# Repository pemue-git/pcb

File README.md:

Dieses Werk ist lizenziert unter einer [Creative Commons Namensnennung - Nicht-kommerziell - Weitergabe unter gleichen Bedingungen 4.0 International Lizenz](http://creativecommons.org/licenses/by-nc-sa/4.0/).

# PCB
This repository contains several PCBs for home automation, discussions see FHEM forum: [forum.fhem.de](https://forum.fhem.de)

## Communication PCB for a Panasonic heat pump
Communication PCB for a Panasonic WH-MDC05f3e5 heat pump also called "Geisha": [WH-MDC05F3E5_comm](WH-MDC05F3E5_comm)

## **L**aCrosse **G**ate**W**ay
ESP8266 based gateway for LaCrosse sensors inlcuding extension PCB.

## nanoCUL
Several versions for a CC1101 USB Light

## Optolink
Interface for Viessmann heating and solar controls (USB, RaspberryPi and WLAN)

Firmware for Optolink interface can be found in [vitotronic-interface](https://github.com/pemue-git/vitotronic_interface).

## Homematic sensors
Several versions of Homematic sensors for usage inside and outside:

Based on [Dirk's version](https://wiki.fhem.de/wiki/Universalsensor) of the sensor, several modifications of the [outside sensor](homematic/aussensensor) have been made.

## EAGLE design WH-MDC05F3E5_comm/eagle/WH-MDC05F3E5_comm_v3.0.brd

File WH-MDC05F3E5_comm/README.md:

# Communication PCB for a Panasonic heat pump
Communication PCB for a Panasonic [WH-MDC05f3e5](http://aquarea.smallsolutions.de/index.php?title=WH-MDC05f3e5) heat pump also called "Geisha". This PCB is based on a schematic posted [here](https://forum.fhem.de/index.php/topic,80916.msg879068.html#msg879068).

# Changelog

* v2.0 (throughole version)
  * based on this [schematic](https://forum.fhem.de/index.php/topic,80916.msg879068.html#msg879068)
  * added static signal on unused gates
  * schematic

* v3.0 (SMD version)
  * all parts changed to SMD
  * layout top

  * layout bottom

  * assembled PCB and USB2serial converter

  * assembled PCB and USB2serial converter (Waveshare)

  * assembled PCB and USB2serial converter (bottom view)

  * [schematic](WH-MDC05F3E5_comm_v3.0_sch.pdf)
  * [gerber files](gerber/WH-MDC05F3E5_comm_v3.0_gerber.zip)
  * [bill of material](WH-MDC05F3E5_comm_v3.0_bom.xls)

# Assembly
__CAUTION__: Pin 1 marking of 4011B is a chamfer at the IC package, indicating the position of pin 1 (chamfer at the left).  
Necessary for the communication is an USB2serial converter (needed signals: 3.3 V, GND, RxD, TxD and __RTS__). The controller chip needs to be a [CP2102](https://www.silabs.com/documents/public/data-sheets/CP2102-9.pdf) and __RTS__ pin needs to be available. The baud rate needs to be set to [960 baud](https://forum.fhem.de/index.php/topic,80916.msg729625.html#msg729625).
An example for a suitable USB2serial converter is [here](https://www.reichelt.de/entwicklerboards-microusb-buchse-auf-uart-cp2102-debo-musb2uart-2-p266052.html?CCOUNTRY=445&LANGUAGE=de&trstct=pos_0&nbc=1&&r=1).

# Modification
The schematic and board files are compatible with EAGLE v6.x.

# Resources
* [WH-MDC05f3e5 documents](http://aquarea.smallsolutions.de/index.php?title=WH-MDC05f3e5#Links_zu_Original_Dokumenten)
* [WiFi module for WH-MDC05f3e5](https://www.haustechnikdialog.de/Forum/t/181931/Intensishome-Wifi-Modul-in-Kombination-mit-der-Panasonic-WH-MDC05F3E5-Geisha) and discussion in Haustechnik Forum
* [PCB hardware discussion](https://forum.fhem.de/index.php/topic,104628.msg985249.html#msg985249) in FHEM forum
* [setup of communcation PCB](https://forum.fhem.de/index.php/topic,80916.msg729625.html#msg729625) in FHEM forum
* [FHEM control](http://aquarea.smallsolutions.de/index.php?title=Steuerung_via_FHEM) in aquarea forum
* [FHEM module](https://github.com/der-lolo/aquarea)
* [Tweakers forum](https://gathering.tweakers.net/forum/list_message/64194378#64194378) (NL)
* for documentation purposes: [online check of MD files](https://dillinger.io/)

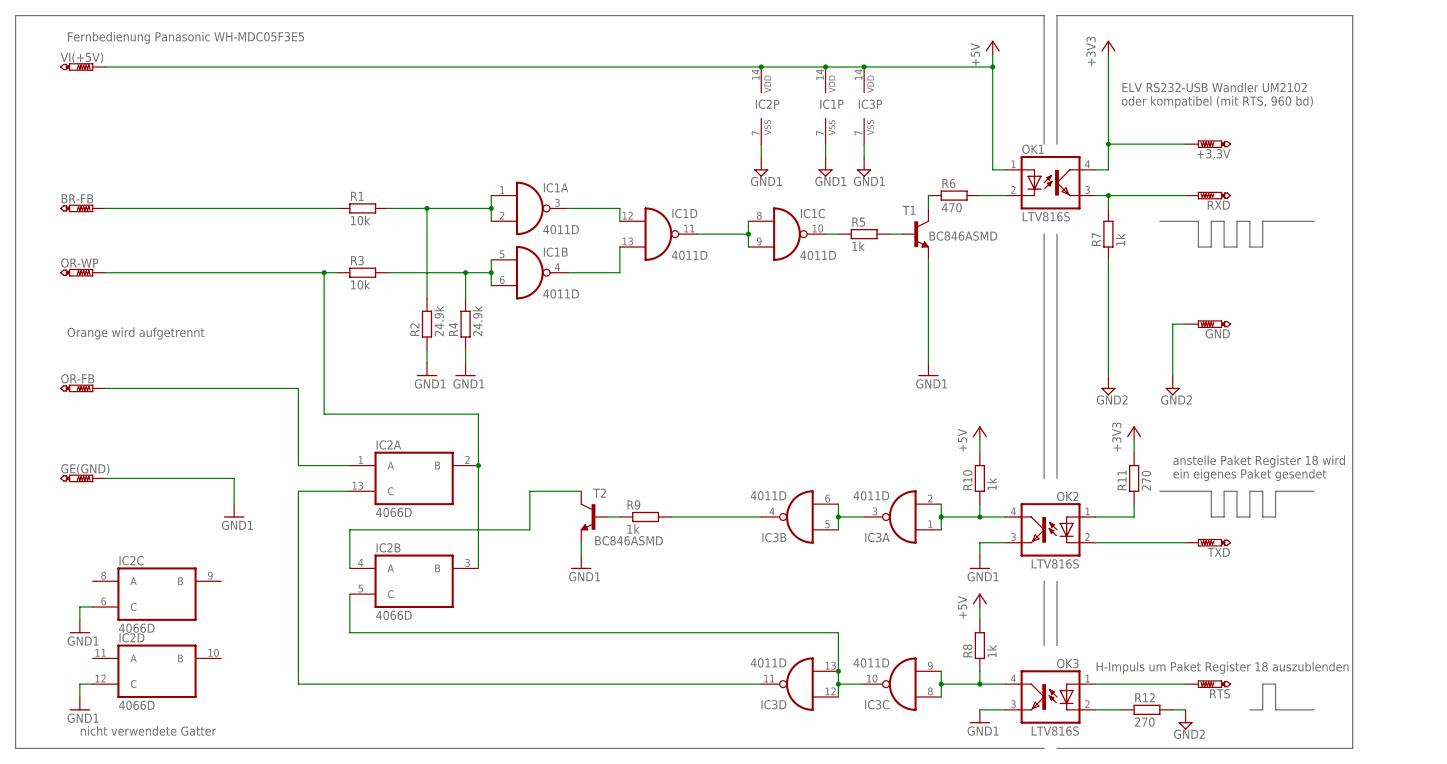
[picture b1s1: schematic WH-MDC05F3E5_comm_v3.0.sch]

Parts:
+3,3V: PTR1PAD1-17; P1-17
BR-FB: PTR1PAD1-17; P1-17
GE(GND): PTR1PAD1-17; P1-17
GND: PTR1PAD1-17; P1-17
IC1, IC3: 4011D; SO14
IC2: 4066D; SO14
OK1, OK2, OK3: LTV816S; SMD4
OR-FB: PTR1PAD1-17; P1-17
OR-WP: PTR1PAD1-17; P1-17
R1, R3: 10k; R0805
R2, R4: 24.9k; R0805
R5, R7, R8, R9, R10: 1k; R0805
R6: 470; R0805
R11, R12: 270; R0805
RTS: PTR1PAD1-17; P1-17
RXD: PTR1PAD1-17; P1-17
T1, T2: BC846ASMD; SOT23
TXD: PTR1PAD1-17; P1-17
VI(+5V): PTR1PAD1-17; P1-17

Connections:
+3V3: +3,3V.TP, OK1.4 (COL), R11.2
+5V: IC1.14 (VDD), IC2.14 (VDD), IC3.14 (VDD), OK1.1 (A), R8.2, R10.2, VI(+5V).TP
GND1: GE(GND).TP, IC1.7 (VSS), IC2.6 (C), IC2.7 (VSS), IC2.12 (C), IC3.7 (VSS), OK2.3 (EMIT), OK3.3 (EMIT), R2.1, R4.1, T1.2 (E), T2.2 (E)
GND2: GND.TP, R7.1, R12.2
unnamed: IC1.1 (I0), IC1.2 (I1), R1.2, R2.2
unnamed: IC1.5 (I0), IC1.6 (I1), R3.2, R4.2
unnamed: IC1.3 (O), IC1.12 (I0)
unnamed: IC1.4 (O), IC1.13 (I1)
unnamed: IC1.8 (I0), IC1.9 (I1), IC1.11 (O)
unnamed: IC1.10 (O), R5.1
unnamed: R5.2, T1.1 (B)
unnamed: R6.2, T1.3 (C)
unnamed: OK1.2 (C), R6.1
unnamed: OK1.3 (EMIT), R7.2, RXD.TP
unnamed: IC2.4 (A), T2.3 (C)
unnamed: OK2.1 (A), R11.1
unnamed: IC2.1 (A), OR-FB.TP
unnamed: IC2.2 (B), IC2.3 (B), OR-WP.TP, R3.1
unnamed: BR-FB.TP, R1.1
unnamed: OK2.2 (C), TXD.TP
unnamed: IC2.13 (C), IC3.11 (O)
unnamed: IC3.8 (I0), IC3.9 (I1), OK3.4 (COL), R8.1
unnamed: IC2.5 (C), IC3.10 (O), IC3.12 (I0), IC3.13 (I1)
unnamed: OK3.2 (C), R12.1
unnamed: OK3.1 (A), RTS.TP
unnamed: IC3.1 (I0), IC3.2 (I1), OK2.4 (COL), R10.1
unnamed: IC3.3 (O), IC3.5 (I0), IC3.6 (I1)
unnamed: R9.1, T2.1 (B)
unnamed: IC3.4 (O), R9.2

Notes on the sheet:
Fernbedienung Panasonic WH-MDC05F3E5
ELV RS232-USB Wandler UM2102 oder kompatibel (mit RTS, 960 bd)
H-Impuls um Paket Register 18 auszublenden
Orange wird aufgetrennt
anstelle Paket Register 18 wird ein eigenes Paket gesendet
nicht verwendete Gatter

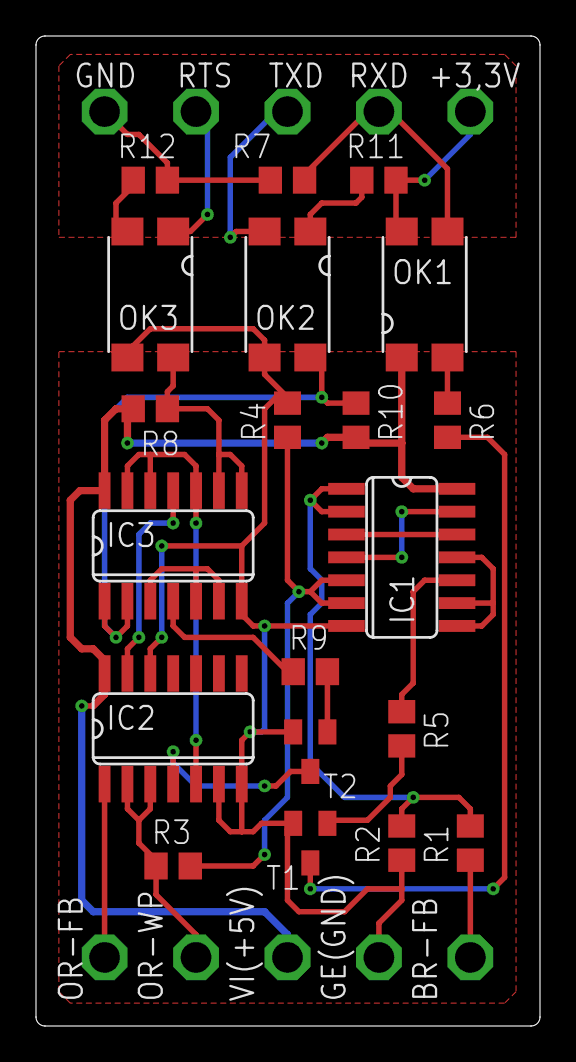
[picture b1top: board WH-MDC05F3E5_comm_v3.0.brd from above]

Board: 2 copper layers, 28.0 x 55.0 mm, 30 parts (0 on the bottom side), 29 nets.

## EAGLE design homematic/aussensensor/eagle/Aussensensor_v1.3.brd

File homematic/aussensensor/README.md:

# Homematic
This repository contains several PCBs for Homematic sensors for usage outside (*Aussensensor*).

## Aussensensor
This layout is based on Dirk's *Universalsensor* described [here](https://wiki.fhem.de/wiki/Universalsensor).

v1.2 schematic of the layout can be found [here](https://github.com/kc-GitHub/Wettersensor/blob/master/Schematic/Universal-Sensor_Atmega328.sch) and board [here](https://github.com/kc-GitHub/Wettersensor/blob/master/Schematic/Universal-Sensor_Atmega328.brd).

v1.2 gerber files can be found [here](Aussensensor_v1.2_gerber).

### Changelog

* v1.3 (06/15/2018, PeMue)
  * GDO2 of CC1101 module connected to D3
  * BME280 added (temperature, pressure, humidity)

* v1.4 (07/09/2018, PeMue)
  * GDO2 removed, added additional capacitor to CC1101 module
  * DS18B20 and pullup to 3.3 V connected to D3, supply voltage is 3.3V
  * added additional tantalum capacitor to MAX1724 output
  * changed pinout of I2C connector to match pinning of MAX44009 light sensor module
  * added SJ2 for battery voltage measurement w/o battery load
  * layout (top)
    
  * layout (bot)

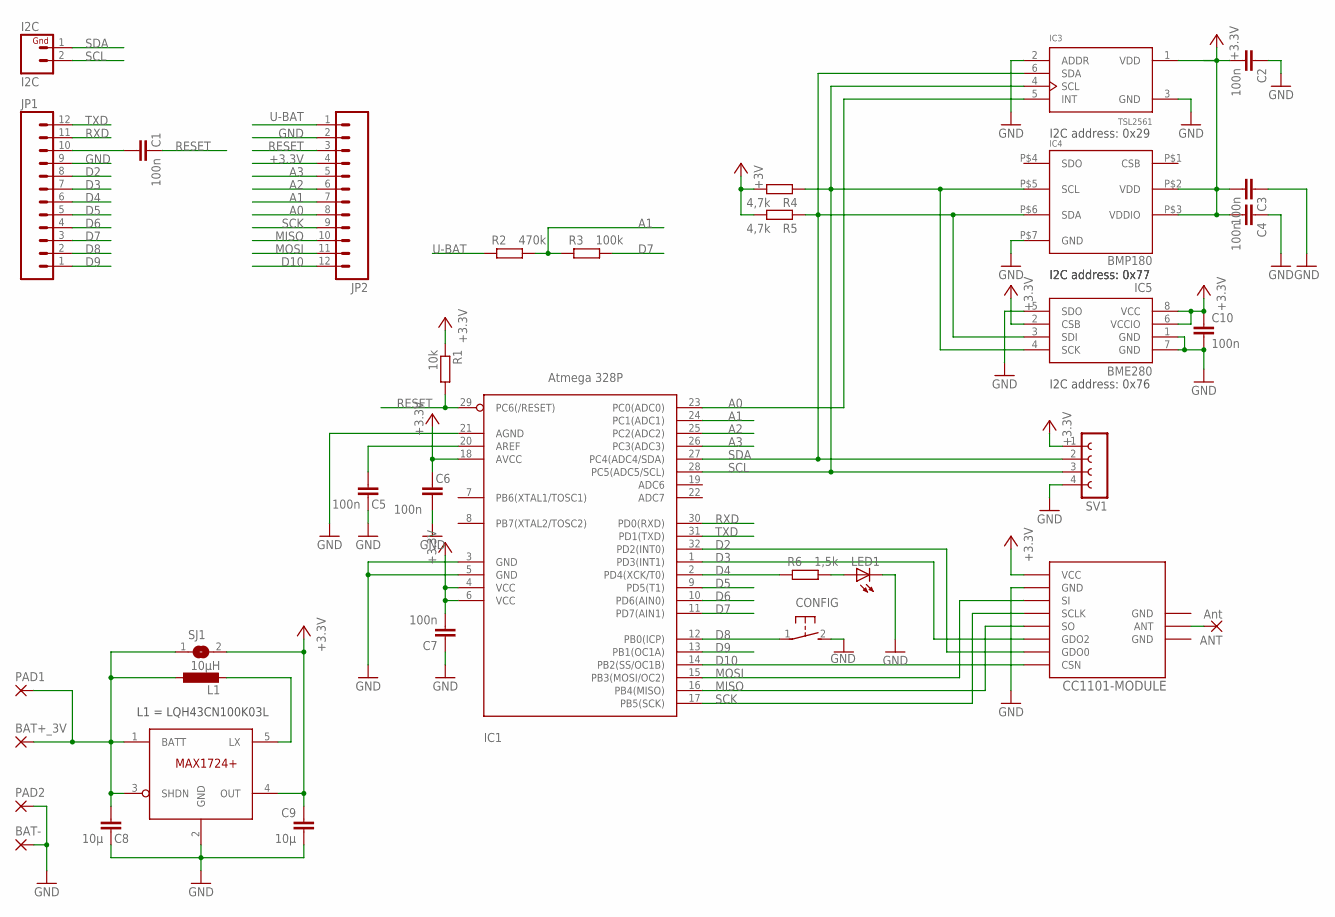
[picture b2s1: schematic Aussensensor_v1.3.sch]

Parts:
ANT: Ant; 1,6/0,8
BAT+_3V: 1,6/0,9
BAT-: 1,6/0,9
C1, C2, C3, C4, C5, C6, C7, C10: 100n; C0805
C8, C9: 10µ; C1206
CC1101-MODULE: CC1101_WIRELES_MODULE
CONFIG: DTSM-3
I2C: I2C; 1X02
IC1: Atmega 328P; TQFP32-08
IC2: MAX1724; SOT23-5L
IC3: TSL2561; TMB-6
IC4: BMP180; LGA-7
IC5: BME280; LGA_8PIN_25X25
JP1, JP2: M12PTH; 1X12
L1: 10µH; L4532P
LED1: LEDCHIP-LED0805; CHIP-LED0805
PAD1, PAD2: SMD2; SMD1,27-2,54
R1: 10k; M0805
R2: 470k; M0805
R3: 100k; M0805
R4, R5: 4,7k; M0805
R6: 1,5k; M0805
SJ1: SJ
SV1: FE04-1

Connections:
+3.3V: C2.2, C3.2, C4.2, C6.2, C7.2, C9.2, C10.1, CC1101-MODULE.VCC, IC1.4 (VCC), IC1.6 (VCC), IC1.18 (AVCC), IC2.4 (OUT), IC3.1 (VDD), IC4.P$2 (VDD), IC4.P$3 (VDDIO), IC5.2 (CSB), IC5.6 (VCCIO), IC5.8 (VCC), JP2.4, R1.1, R4.2, R5.2, SJ1.2, SV1.1
A0: IC1.23 (PC0(ADC0)), IC3.5 (INT), JP2.8
A1: IC1.24 (PC1(ADC1)), JP2.7, R2.2, R3.1
A2: IC1.25 (PC2(ADC2)), JP2.6
A3: IC1.26 (PC3(ADC3)), JP2.5
D2: CC1101-MODULE.GDO0, IC1.32 (PD2(INT0)), JP1.8
D3: CC1101-MODULE.GDO2, IC1.1 (PD3(INT1)), JP1.7
D4: IC1.2 (PD4(XCK/T0)), JP1.6, R6.1
D5: IC1.9 (PD5(T1)), JP1.5
D6: IC1.10 (PD6(AIN0)), JP1.4
D7: IC1.11 (PD7(AIN1)), JP1.3, R3.2
D8: CONFIG.1, IC1.12 (PB0(ICP)), JP1.2
D9: IC1.13 (PB1(OC1A)), JP1.1
D10: CC1101-MODULE.CSN, IC1.14 (PB2(SS/OC1B)), JP2.12
GND: BAT-.1, C2.1, C3.1, C4.1, C5.1, C6.1, C7.1, C8.1, C9.1, C10.2, CC1101-MODULE.GND@1 (GND), CC1101-MODULE.GND@2 (GND), CC1101-MODULE.GND@3 (GND), CONFIG.2, IC1.3 (GND), IC1.5 (GND), IC1.21 (AGND), IC2.2 (GND), IC3.2 (ADDR), IC3.3 (GND), IC4.P$7 (GND), IC5.1 (GND), IC5.5 (SDO), IC5.7 (GND), JP1.9, JP2.2, LED1.C, PAD2.1, SV1.4
MISO: CC1101-MODULE.SO, IC1.16 (PB4(MISO)), JP2.10
MOSI: CC1101-MODULE.SI, IC1.15 (PB3(MOSI/OC2)), JP2.11
unnamed: C1.2, JP1.10
unnamed: IC2.5 (LX), L1.2
unnamed: LED1.A, R6.2
unnamed: ANT.1, CC1101-MODULE.ANT
unnamed: C5.2, IC1.20 (AREF)
RESET: C1.1, IC1.29 (PC6(/RESET)), JP2.3, R1.2
RXD: IC1.30 (PD0(RXD)), JP1.11
SCK: CC1101-MODULE.SCLK, IC1.17 (PB5(SCK)), JP2.9
SCL: I2C.2, IC1.28 (PC5(ADC5/SCL)), IC3.4 (SCL), IC4.P$5 (SCL), IC5.4 (SCK), R4.1, SV1.3
SDA: I2C.1, IC1.27 (PC4(ADC4/SDA)), IC3.6 (SDA), IC4.P$6 (SDA), IC5.3 (SDI), R5.1, SV1.2
TXD: IC1.31 (PD1(TXD)), JP1.12
U-BAT: BAT+_3V.1, C8.2, IC2.1 (BATT), IC2.3 (SHDN), JP2.1, L1.1, PAD1.1, R2.1, SJ1.1

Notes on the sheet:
L1 = LQH43CN100K03L
I2C address: 0x29
I2C address: 0x77
I2C address: 0x76

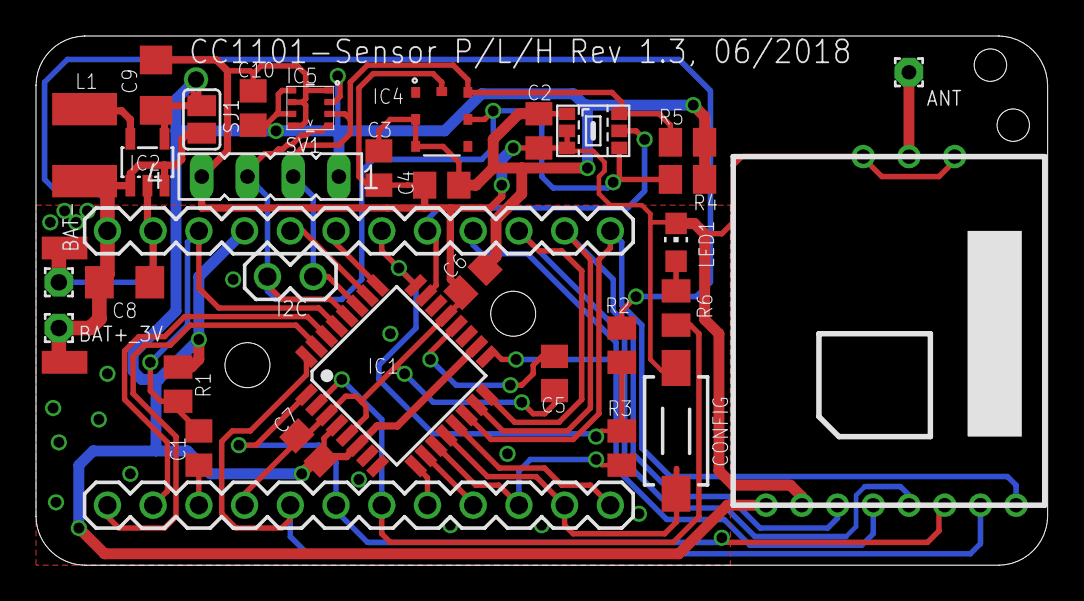
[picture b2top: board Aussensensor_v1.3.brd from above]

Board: 2 copper layers, 56.2 x 29.4 mm, 35 parts (0 on the bottom side), 29 nets.

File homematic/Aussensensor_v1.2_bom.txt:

Stückliste Außensensor v1.2
---------------------------
Part          Value                 Device                Package               
C1            100n                  C-EUC0805             C0805                 
C2            100n                  C-EUC0805             C0805                 
C3            100n                  C-EUC0805             C0805                 
C4            100n                  C-EUC0805             C0805                 
C5            100n                  C-EUC0805             C0805                 
C6            100n                  C-EUC0805             C0805                 
C7            100n                  C-EUC0805             C0805                 
C8            10µ                   C-EUC1206             C1206                 
C9            10µ                   C-EUC1206             C1206                 
R1            10k                   R-EU_M0805            M0805                 
R2            470k                  R-EU_M0805            M0805                 
R3            100k                  R-EU_M0805            M0805                 
R4            4,7k                  R-EU_M0805            M0805                 
R5            4,7k                  R-EU_M0805            M0805                 
R6            1,0k                  R-EU_M0805            M0805                 
LED1          green                 LEDCHIP-LED0805       CHIP-LED0805          
L1            10µH                  L-EUL4532P            L4532P                
CONFIG        DTSM-3                DTSM-3                DTSM-3                
IC1           Atmega 328P           MEGA8-AI              TQFP32-08             
IC2           MAX1724               MAX1724               SOT23-5L              
IC3           TSL2561               TSL2560               TMB-6                 
IC4           BMP180                BMP180                LGA-7                 
CC1101-MODULE                       CC1101 module         SMD module
ANT           Ant                   1,6/0,8               1,6/0,8               

not used
BAT+_3V                             1,6/0,9               1,6/0,9               
BAT-                                1,6/0,9               1,6/0,9               
PAD1                                SMD2                  SMD1,27-2,54          
PAD2                                SMD2                  SMD1,27-2,54          
JP1                                 M12PTH                1X12                  
JP2                                 M12PTH                1X12                  
I2C           I2C                   M02PTH                1X02                  
SV1                                 FE04-1                FE04-1                
SJ1                                 SJ                    SJ

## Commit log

2018-07-05 upload complete stuff after deleting repository
2018-07-09 added SJ2 for battery voltage measurement w/o battery load
2018-08-18 - added gerber files of Aussensensor v1.2 layout (Dirk) - added pictures of Aussensensor v1.4 layout
2018-08-18 change README.md
2018-08-18 - added Aussensenso v1.2 BOM in text format
2018-08-18 - changed Aussensensor_v1.4.brd
2018-08-18 - added Aussensensor_v1.4_sch.pdf
2018-08-23 - add Außensensor v1.5 eagle files (first try)
2018-08-31 - changes requested by Tom Major
2018-09-06 Preview Dateien für Version 1.6
2018-09-19 - delete preview pictures of v1.6 (Target)
2018-09-20 - remove preview pictures for v1.51 (Target)
2018-10-26 Changed compared to previous version: - all vias diameter 0.7, drill 0,4 mm - moved vias for buffer capacitor C3 and C11 - improved layout for C6 - R9 (pull up for CSN) added
2018-12-11 add correspondig brd file to Aussensensor_v1.4.sch
2018-12-11 replaced 10k by 4k7 for DS18x20 in Aussensensor v1.4 and v1.5
2019-06-06 replace Aussensensor v1.5 with a better readable schematic (no layout change)
2019-06-16 changes to previous: - update Aussensensor_v1.5_bom.xls
2019-06-16 changes to previous version: - Aussensensor_v1.5_bom.xls corrected
2019-06-18 Changes to previous version: - updated R-divider for voltage measurement in Aussensensor_v1.5_bom.xls and the eagle files, printed PDF of schematic (Aussensensor_v1.5_sch.pdf)
2019-06-20 Changes to previous version: - some cosmetical correction in schematic of Aussensensor_v1.5.sch
2019-08-16 relicened under CC BY-ND-SA
2019-08-16 added first version of RFM95 breakout board (stolen from Adafrout)
2019-11-27 added first version of ESP RGBWW controller v2.5 PCB
2019-11-27 added first version of ESP RGBWW controller v2.5 PCB (updated README.md)
2019-12-22 updated ESP_RGBWW_controller/README.md
2020-01-17 change structure and some typos
2020-01-17 change structure, correct typos
2020-01-17 update ESP_RGBWW_controller READ
2020-03-20 changed - added complete documentation of WH-MDC05F3E5_comm PCB (v2.0, v3.0)
2020-03-20 changed README.md
2020-05-15 change to previous version: - README.md: typos and marked topics in work
2020-05-15 changes to previous version: - README.md: corrected path
2020-05-15 changes to previoous version: - README.md: smaller picture
2020-05-15 changes to previous version: - README.md: resized images
2020-05-15 changes to previous version: - updated README.md: resized images
2020-05-15 changes to previous versions: - README.md: typos
2020-05-17 changes to previous version: - updated README.md, aussensensor/README.md and WH-MDC05F3E5_comm/README.md
2020-05-18 changes to previous version: - added aussensensor/Aussensensor_v1.6_sch.pdf w/o further documentation (tbd.)
2020-06-06 changes to previous version: - added Innensensor_v1.4_sch.pdf and Innensensor_v1.4_bom.xls (w/o further documentation - changed Aussensensor_v1.5_bom.xls
2020-07-15 changes to previous version: - added FHEM links for WH-MDC05F3E5 to README.md
2020-07-24 change to previous version: - update README.md (add CP2102 USB serial converter)
2020-07-24 changes to previous version: - added BOM WH-MDC05F3E5_comm_v3.0_bom.xls - changed readme (BOM, typos)
2020-07-26 change to previous version: - added files for uAmperemeter (v1.0 and v1.1), README.md missing
2020-08-08 changes to previous version: - added BOMs for v1.0 and v1.1
2020-08-13 change to previous version: - added README.md and eagle files for v1.1
2020-08-13 change to previous version: - rename directory (typo)
2020-08-13 change to previous version: - add README.md
2020-08-13 change to previous version: - correct type (pads) in README.md
2020-11-09 changes to previous version: - README.md: added note for 4011, added link for tweakers forum, corrected links
2020-11-09 changes to previous version: - corrected typos in README.md
2020-11-09 change to previous version: - correct directory of uAmperemeter
2020-11-22 change to previous version: - added pin 1 chamfer notice in schematics - added link to a suitable USB2serial converter - additional pictures
2020-11-23 changes to previous version: - update schematics (comments)

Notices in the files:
README.md:
Creative Commons Lizenzvertrag
parts and their libraries:
eagle-library-edeca.net-v5: This is v1 and is licensed under the Creative Commons (Attribution-Non-Commercial-Share Alike 2.0 UK)
